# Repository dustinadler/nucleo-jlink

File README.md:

# nucleo-jlink

ST Nucleo + SEGGER Jlink SWD adapter 

Format is EagleCAD schematic and board layout

Adapts Jlink 2x10 connector to the 6-pin ARM SWD connector on the larger ST Nucleo development boards.

### Notes

Target Vref is connected to JP1 on the Nucleo PCB, which is normally left open. JP1 controls the max current requested during USB enumeration. You may need to short it if you are powering the board via USB without enumeration. If you wish to short this jumper, use extended-length header pins or simply bridge the pins on the adapter PCB. 

### PCB on OSH Park

You can order a PCB for this adapter [on OSH Park](https://oshpark.com/shared_projects/m3tkYXXR).

### More Information

* https://www.segger.com/admin/uploads/productDocs/UM08001_JLink.pdf
* https://wiki.segger.com/index.php?title=Connecting_to_STM32_Nucleo_boards
* http://www2.st.com/content/ccc/resource/technical/document/user_manual/98/2e/fa/4b/e0/82/43/b7/DM00105823.pdf/files/DM00105823.pdf/jcr:content/translations/en.DM00105823.pdf

### License

This is free and unencumbered software released into the public domain.

Anyone is free to copy, modify, publish, use, compile, sell, or
distribute this software, either in source code form or as a compiled
binary, for any purpose, commercial or non-commercial, and by any
means.

In jurisdictions that recognize copyright laws, the author or authors
of this software dedicate any and all copyright interest in the
software to the public domain. We make this dedication for the benefit
of the public at large and to the detriment of our heirs and
successors. We intend this dedication to be an overt act of
relinquishment in perpetuity of all present and future rights to this
software under copyright law.

THE SOFTWARE IS PROVIDED "AS IS", WITHOUT WARRANTY OF ANY KIND,
EXPRESS OR IMPLIED, INCLUDING BUT NOT LIMITED TO THE WARRANTIES OF
MERCHANTABILITY, FITNESS FOR A PARTICULAR PURPOSE AND NONINFRINGEMENT.
IN NO EVENT SHALL THE AUTHORS BE LIABLE FOR ANY CLAIM, DAMAGES OR
OTHER LIABILITY, WHETHER IN AN ACTION OF CONTRACT, TORT OR OTHERWISE,
ARISING FROM, OUT OF OR IN CONNECTION WITH THE SOFTWARE OR THE USE OR
OTHER DEALINGS IN THE SOFTWARE.

For more information, please refer to <http://unlicense.org>

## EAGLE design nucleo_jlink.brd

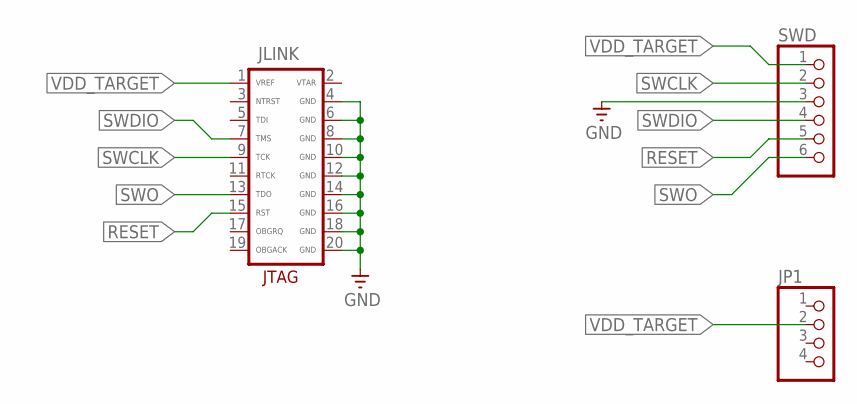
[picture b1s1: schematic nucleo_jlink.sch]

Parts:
JLINK: JTAG-ARM
JP1: PINHD-1X4; 1X04
SWD: PINHD-1X6; 1X06

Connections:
GND: JLINK.4 (GND), JLINK.6 (GND), JLINK.8 (GND), JLINK.10 (GND), JLINK.12 (GND), JLINK.14 (GND), JLINK.16 (GND), JLINK.18 (GND), JLINK.20 (GND), SWD.3
RESET: JLINK.15 (RST), SWD.5
SWCLK: JLINK.9 (TCK), SWD.2
SWDIO: JLINK.7 (TMS), SWD.4
SWO: JLINK.13 (TDO), SWD.6
VDD_TARGET: JLINK.1 (VREF), JP1.2, SWD.1

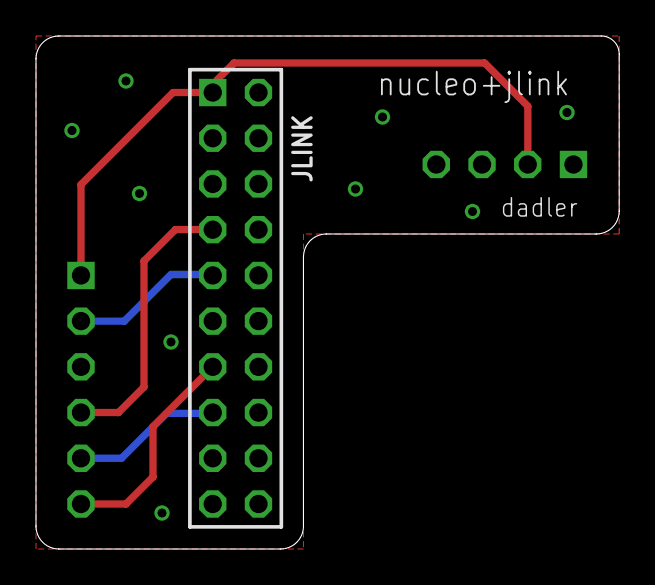
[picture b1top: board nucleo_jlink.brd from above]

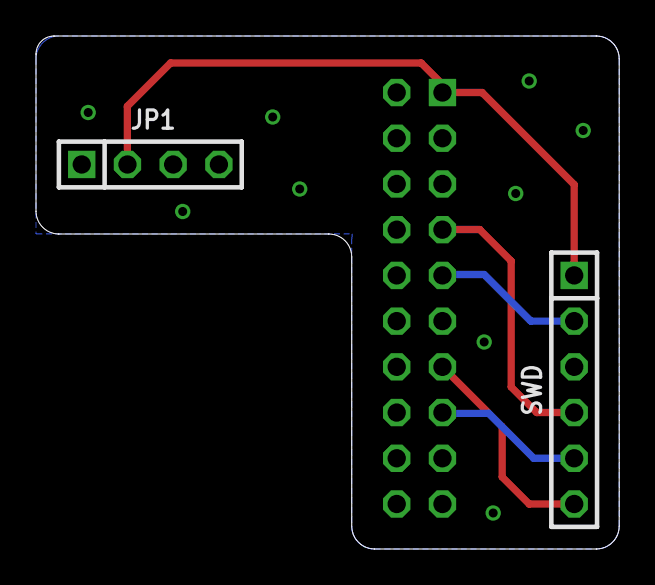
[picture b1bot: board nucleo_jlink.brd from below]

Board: 2 copper layers, 32.4 x 28.5 mm, 3 parts (2 on the bottom side), 6 nets.

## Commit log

2016-04-18 commit layout+schematic
